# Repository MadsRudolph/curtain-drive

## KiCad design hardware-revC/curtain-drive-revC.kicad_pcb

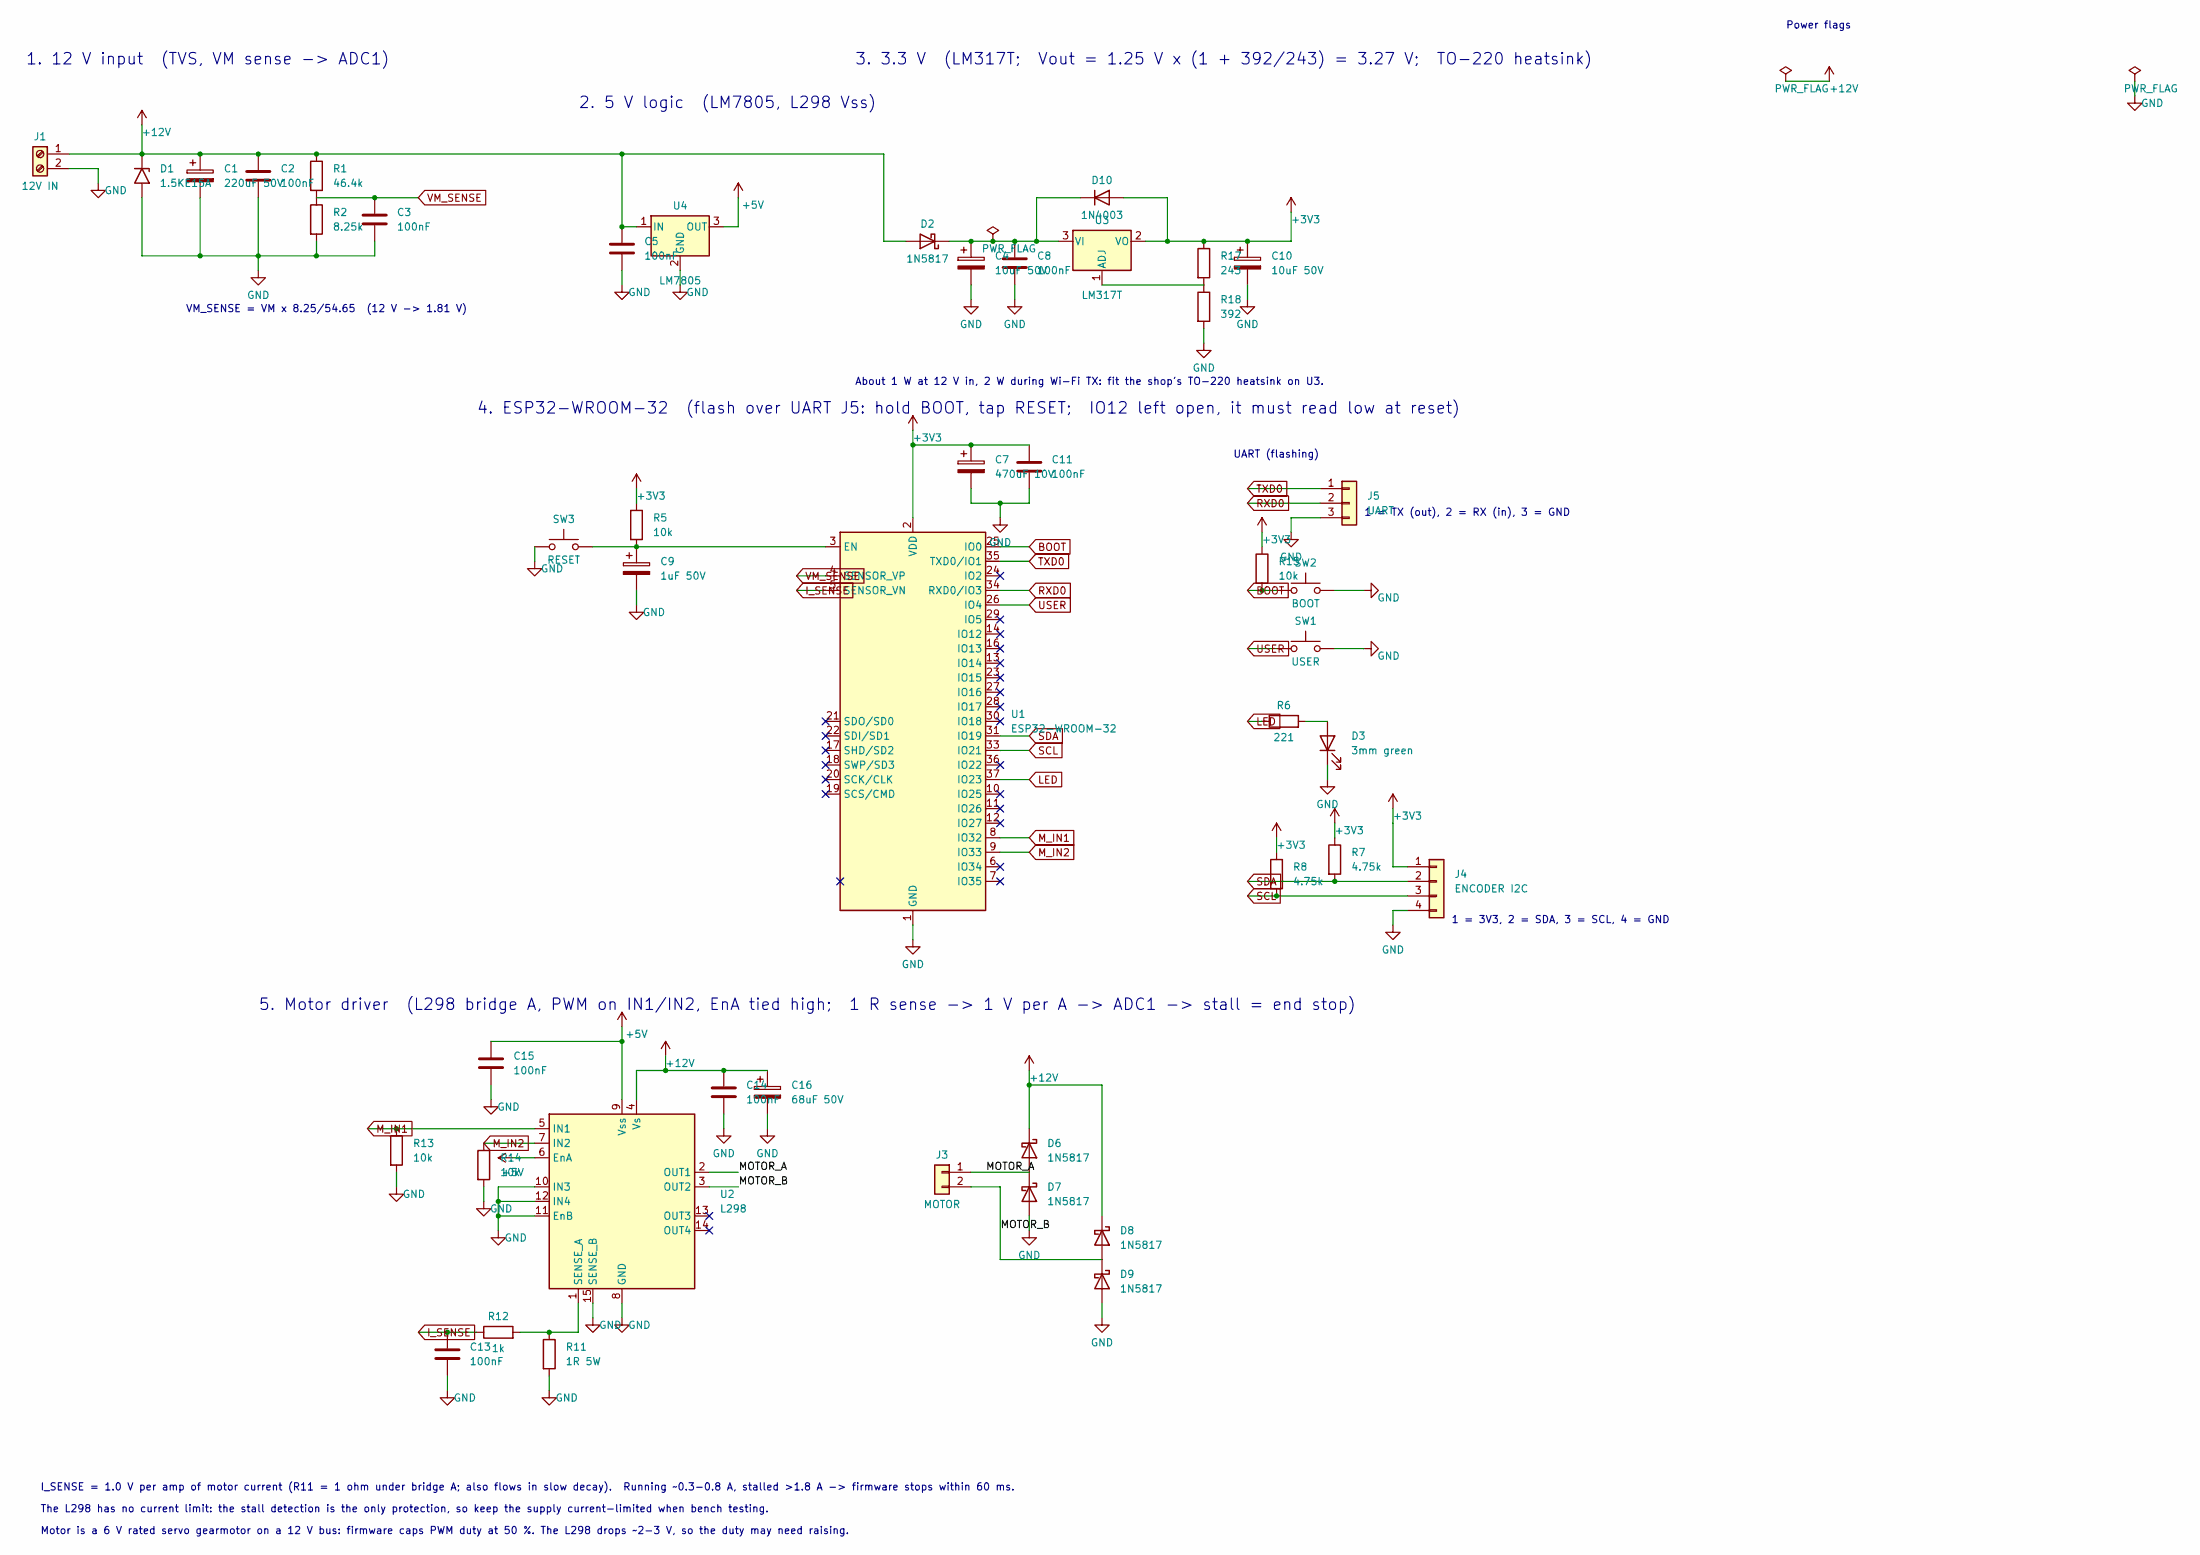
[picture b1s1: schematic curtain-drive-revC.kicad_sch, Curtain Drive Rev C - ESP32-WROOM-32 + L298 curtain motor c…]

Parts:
C1: 220uF 50V; CP_Radial_D10.0mm_P5.00mm
C2, C3, C5, C8, C11, C13, C15: 100nF; C_Disc_D5.0mm_W2.5mm_P5.00mm
C4, C10: 10uF 50V; CP_Radial_D5.0mm_P2.00mm
C7: 470uF 10V; CP_Radial_D8.0mm_P3.50mm
C9: 1uF 50V; CP_Radial_D5.0mm_P2.00mm
C14: 100nF; C_Disc_D5.0mm_W2.5mm_P7.62mm_Bent
C16: 68uF 50V; CP_Radial_D8.0mm_P3.50mm
D1: 1.5KE15A; D_DO-201AE_P15.24mm_Horizontal
D2, D6, D7, D8, D9: 1N5817; D_DO-41_SOD81_P10.16mm_Horizontal
D3: 3mm green; LED_D3.0mm
D10: 1N4003; D_DO-41_SOD81_P10.16mm_Horizontal
J1: 12V IN; TerminalBlock_Phoenix_MKDS-1,5-2-5.08_1x02_P5.08mm_Horizont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
J3: MOTOR; Molex_KK-254_AE-6410-02A_1x02_P2.54mm_Vertical
J4: ENCODER I2C; Molex_KK-254_AE-6410-04A_1x04_P2.54mm_Vertical
J5: UART; PinHeader_1x03_P2.54mm_Vertical
R1: 46.4k; R_Axial_DIN0207_L6.3mm_D2.5mm_P7.62mm_Horizontal
R2: 8.25k; R_Axial_DIN0207_L6.3mm_D2.5mm_P7.62mm_Horizontal
R5, R13, R14, R15: 10k; R_Axial_DIN0207_L6.3mm_D2.5mm_P7.62mm_Horizontal
R6: 221; R_Axial_DIN0207_L6.3mm_D2.5mm_P7.62mm_Horizontal
R7, R8: 4.75k; R_Axial_DIN0207_L6.3mm_D2.5mm_P7.62mm_Horizontal
R11: 1R 5W; R_Axial_Power_L25.0mm_W9.0mm_P27.94mm
R12: 1k; R_Axial_DIN0207_L6.3mm_D2.5mm_P7.62mm_Horizontal
R17: 243; R_Axial_DIN0207_L6.3mm_D2.5mm_P7.62mm_Horizontal
R18: 392; R_Axial_DIN0207_L6.3mm_D2.5mm_P7.62mm_Horizontal
SW1: USER; SW_PUSH_6mm_Jumpers
SW2: BOOT; SW_PUSH_6mm_Jumpers
SW3: RESET; SW_PUSH_6mm_Jumpers
U1: ESP32-WROOM-32; ESP32-WROOM-32_NoVias
U2: L298; TO-220-15_P2.54x5.08mm_StaggerOdd_Lead4.58mm_Vertical
U3: LM317T; TO-220-3_Vertical_Heatsink16x16
U4: LM7805; TO-220-3_Vertical

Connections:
+3V3: C7.1, C10.1, C11.1, D10.2 (A), J4.1, R5.1, R7.1, R8.1, R15.1, R17.1, U1.2 (VDD), U3.2 (VO)
+5V: C15.1, U2.6 (EnA), U2.9 (Vss), U4.3 (OUT)
/MOTOR_A: D6.2 (A), D7.1 (K), J3.1, U2.2 (OUT1)
/MOTOR_B: D8.2 (A), D9.1 (K), J3.2, U2.3 (OUT2)
BOOT: R15.2, SW2.1, U1.25 (IO0)
I_SENSE: C13.1, R12.1, U1.5 (SENSOR_VN)
LED: R6.1, U1.37 (IO23)
M_IN1: R13.1, U1.8 (IO32), U2.5 (IN1)
M_IN2: R14.1, U1.9 (IO33), U2.7 (IN2)
unnamed: D3.2 (A), R6.2
unnamed: C9.1, R5.2, SW3.2, U1.3 (EN)
unnamed: R11.1, R12.2, U2.1 (SENSE_A)
unnamed: R17.2, R18.1, U3.1 (ADJ)
RXD0: J5.2, U1.34 (RXD0/IO3)
SCL: J4.3, R8.2, U1.33 (IO21)
SDA: J4.2, R7.2, U1.31 (IO19)
TXD0: J5.1, U1.35 (TXD0/IO1)
USER: SW1.1, U1.26 (IO4)
VM_SENSE: C3.1, R1.2, R2.1, U1.4 (SENSOR_VP)

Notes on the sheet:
1. 12 V input (TVS, VM sense -> ADC1)
VM_SENSE = VM x 8.25/54.65 (12 V -> 1.81 V)
2. 5 V logic (LM7805, L298 Vss)
3. 3.3 V (LM317T; Vout = 1.25 V x (1 + 392/243) = 3.27 V; TO-220 heatsink)
About 1 W at 12 V in, 2 W during Wi-Fi TX: fit the shop's TO-220 heatsink on U3.
Power flags
4. ESP32-WROOM-32 (flash over UART J5: hold BOOT, tap RESET; IO12 left open, it must read low at reset)
UART (flashing)
1 = TX (out), 2 = RX (in), 3 = GND
1 = 3V3, 2 = SDA, 3 = SCL, 4 = GND
5. Motor driver (L298 bridge A, PWM on IN1/IN2, EnA tied high; 1 R sense -> 1 V per A -> ADC1 -> stall = end stop)
I_SENSE = 1.0 V per amp of motor current (R11 = 1 ohm under bridge A; also flows in slow decay). Running ~0.3-0.8 A, stalled >1.8 A -> firmware stops within 60 ms.
The L298 has no current limit: the stall detection is the only protection, so keep the supply current-limited when bench testing.
Motor is a 6 V rated servo gearmotor on a 12 V bus: firmware caps PWM duty at 50 %. The L298 drops ~2-3 V, so the duty may need raising.

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
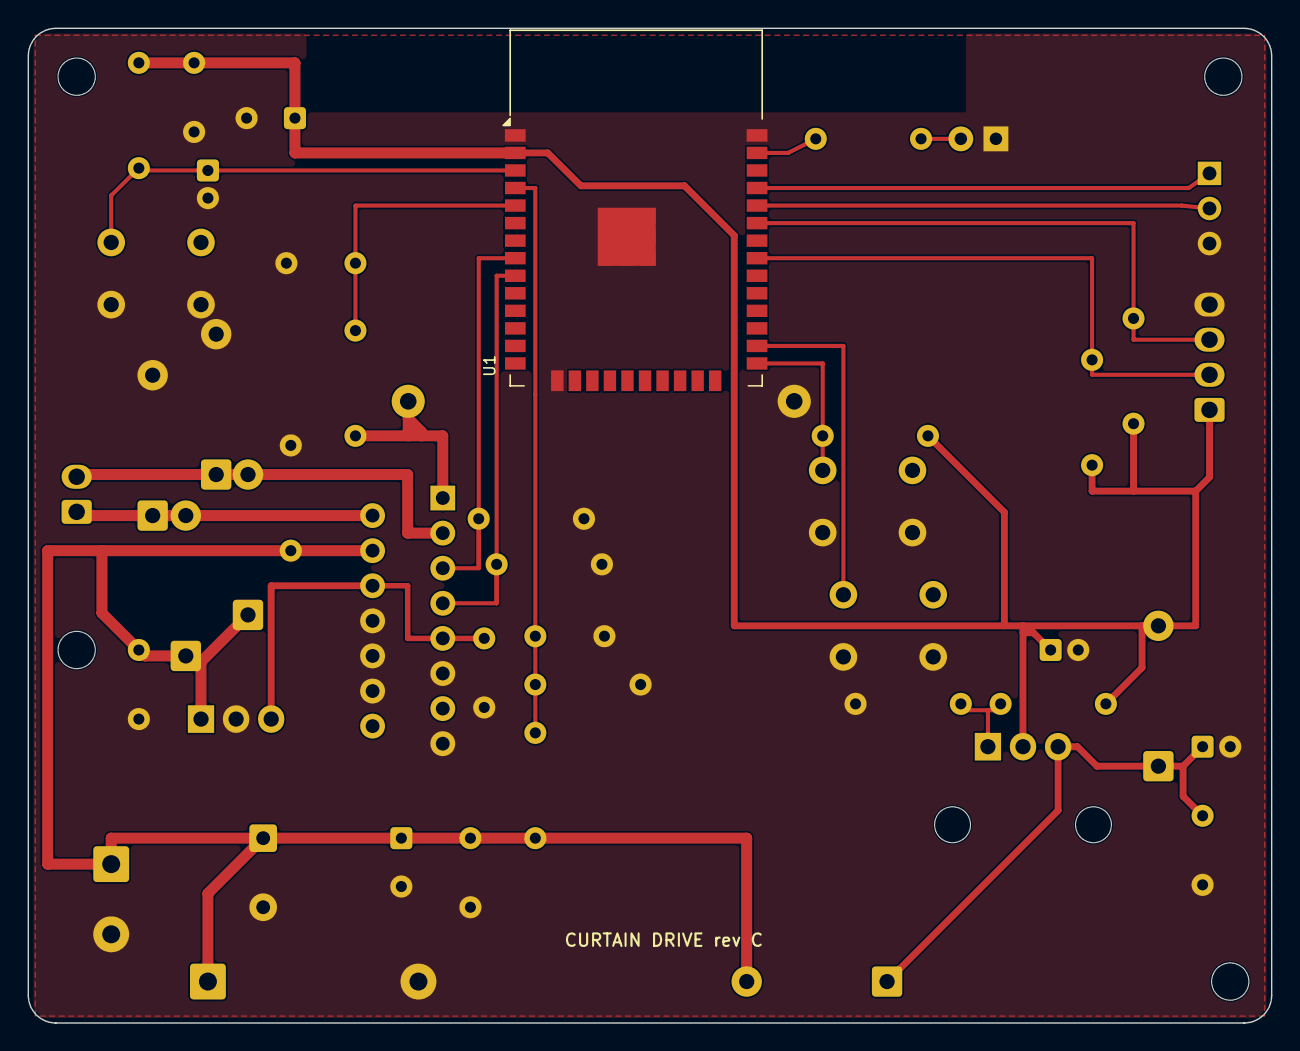
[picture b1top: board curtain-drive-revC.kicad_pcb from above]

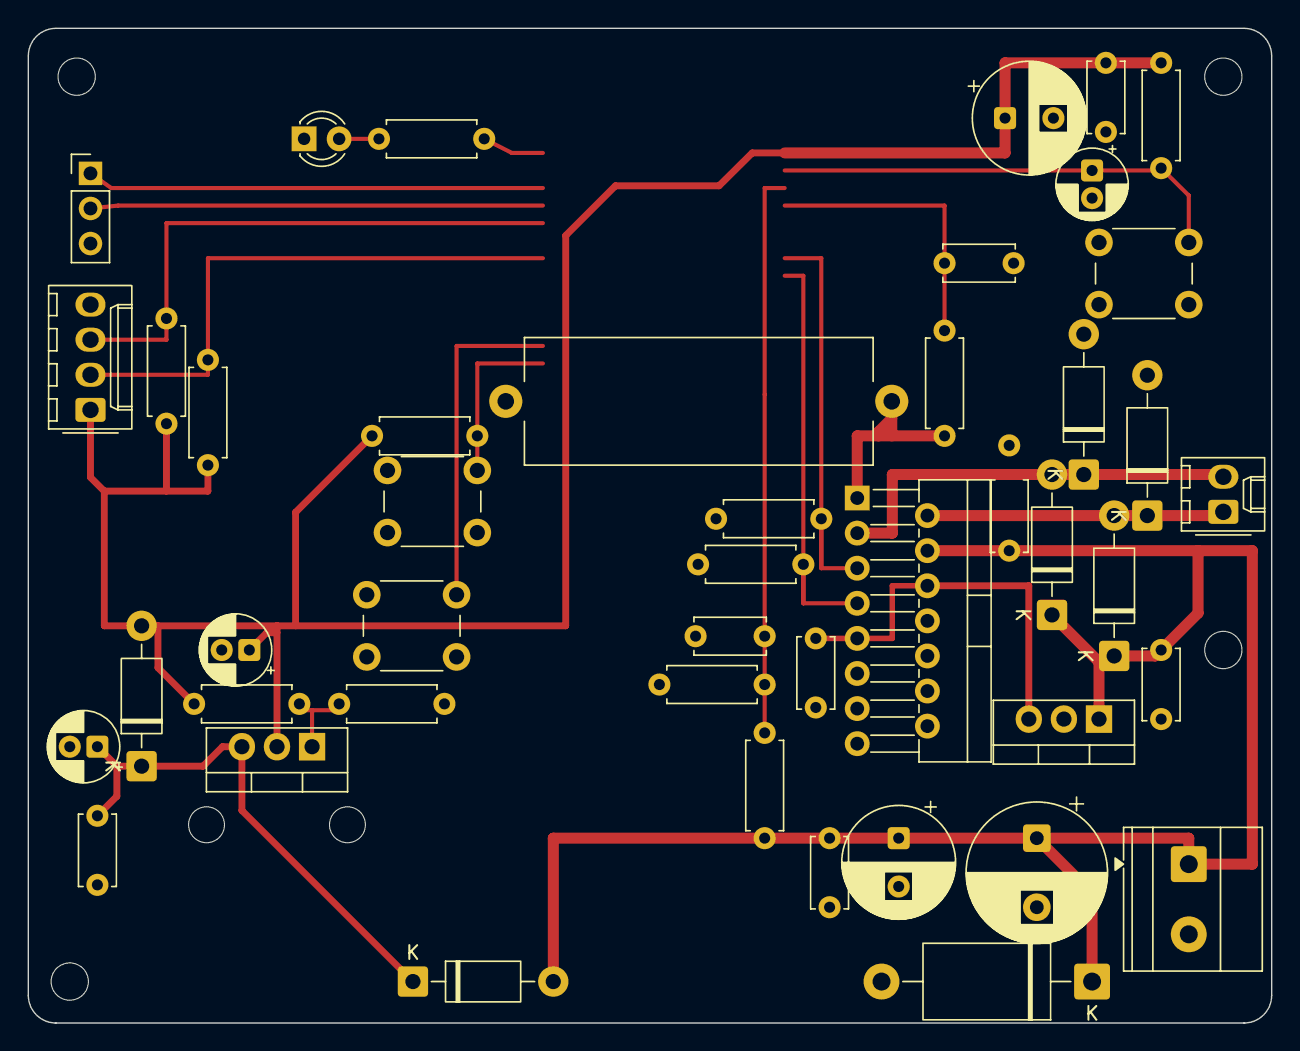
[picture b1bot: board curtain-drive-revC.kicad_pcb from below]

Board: 2 copper layers, 90.0 x 72.0 mm, 50 parts (45 on the bottom side), 22 nets.

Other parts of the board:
H1, H2, H3, H4: MountingHole_2.7mm_M2.5

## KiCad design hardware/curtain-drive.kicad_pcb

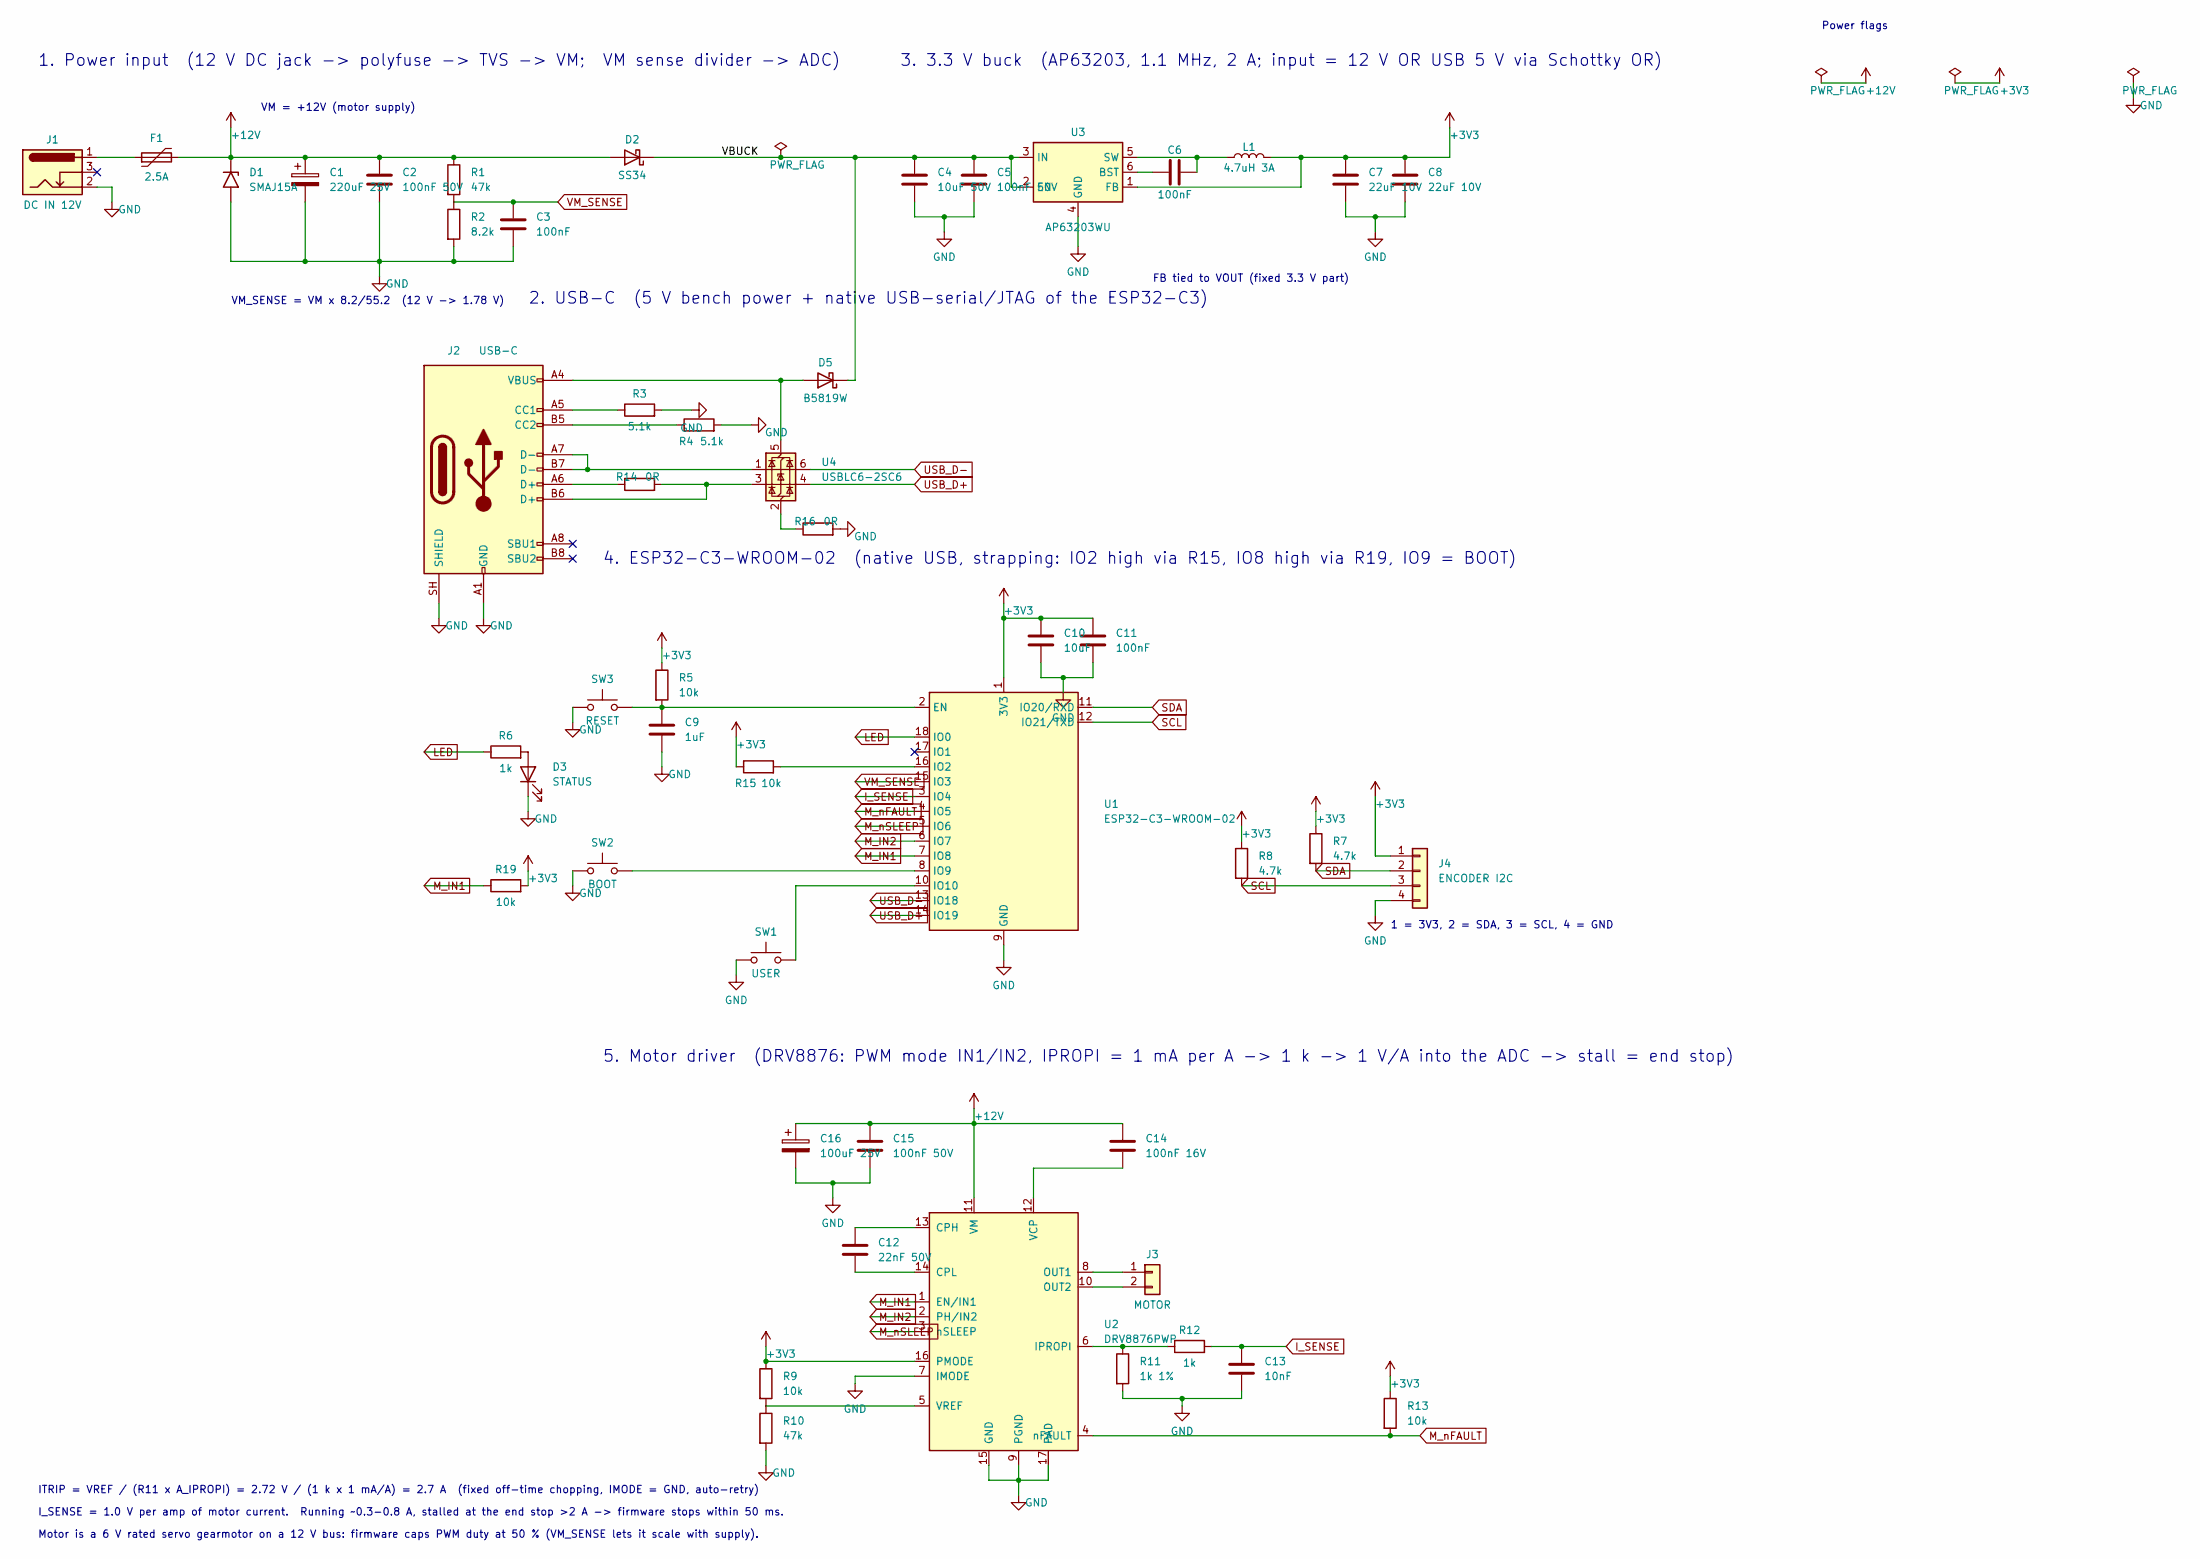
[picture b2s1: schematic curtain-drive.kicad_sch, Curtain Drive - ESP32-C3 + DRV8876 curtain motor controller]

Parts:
C1: 220uF 25V; CP_Elec_8x10
C2, C5, C15: 100nF 50V; C_0603_1608Metric
C3, C6, C11: 100nF; C_0603_1608Metric
C4: 10uF 50V; C_1206_3216Metric
C7, C8: 22uF 10V; C_0805_2012Metric
C9: 1uF; C_0603_1608Metric
C10: 10uF; C_0805_2012Metric
C12: 22nF 50V; C_0603_1608Metric
C13: 10nF; C_0603_1608Metric
C14: 100nF 16V; C_0603_1608Metric
C16: 100uF 25V; CP_Elec_6.3x7.7
D1: SMAJ15A; D_SMA
D2: SS34; D_SMA
D3: STATUS; LED_0603_1608Metric
D5: B5819W; D_SOD-123
F1: 2.5A; Fuse_1812_4532Metric
J1: DC IN 12V; BarrelJack_CUI_PJ-036AH-SMT_Horizontal
J2: USB-C; USB_C_Receptacle_HRO_TYPE-C-31-M-12_1L
J3: MOTOR; JST_PH_B2B-PH-SM4-TB_1x02-1MP_P2.00mm_Vertical
J4: ENCODER I2C; JST_PH_B4B-PH-SM4-TB_1x04-1MP_P2.00mm_Vertical
L1: 4.7uH 3A; L_Sunlord_MWSA0503S
R1: 47k; R_1206_3216Metric
R2: 8.2k; R_0603_1608Metric
R3: 5.1k; R_0805_2012Metric
R4: 5.1k; R_0603_1608Metric
R5, R15, R19: 10k; R_0603_1608Metric
R6, R12: 1k; R_0603_1608Metric
R7, R8: 4.7k; R_0603_1608Metric
R9, R13: 10k; R_0805_2012Metric
R10: 47k; R_0805_2012Metric
R11: 1k 1%; R_0603_1608Metric
R14: 0R; R_0603_1608Metric
R16: 0R; R_0805_2012Metric
SW1: USER; SW_SPST_PTS645Sx43SMTR92_Jumpers
SW2: BOOT; SW_SPST_PTS645Sx43SMTR92_Jumpers
SW3: RESET; SW_SPST_PTS645Sx43SMTR92_Jumpers
U1: ESP32-C3-WROOM-02; ESP32-C3-WROOM-02_NoVias
U2: DRV8876PWP; HTSSOP-16-1EP_4.4x5mm_P0.65mm_EP3.4x5mm_Mask2.46x2.31mm
U3: AP63203WU; TSOT-23-6
U4: USBLC6-2SC6; SOT-23-6

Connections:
I_SENSE: C13.1, R12.2, U1.3 (IO4)
LED: R6.1, U1.18 (IO0)
M_IN1: R19.1, U1.7 (IO8), U2.1 (EN/IN1)
M_IN2: U1.6 (IO7), U2.2 (PH/IN2)
M_nFAULT: R13.2, U1.4 (IO5), U2.4 (nFAULT)
M_nSLEEP: U1.5 (IO6), U2.3 (nSLEEP)
unnamed: D3.2 (A), R6.2
unnamed: D5.2 (A), J2.A4 (VBUS), J2.A9 (VBUS), J2.B4 (VBUS), J2.B9 (VBUS), U4.5 (VBUS)
unnamed: F1.1, J1.1
unnamed: J2.A5 (CC1), R3.1
unnamed: J2.B5 (CC2), R4.1
unnamed: J2.A6 (D+), R14.1
unnamed: J2.B6 (D+), R14.2, U4.3 (I/O2)
unnamed: J2.A7 (D-), J2.B7 (D-), U4.1 (I/O1)
unnamed: J3.1, U2.8 (OUT1)
unnamed: J3.2, U2.10 (OUT2)
unnamed: C9.1, R5.2, SW3.2, U1.2 (EN)
unnamed: R15.2, U1.16 (IO2)
unnamed: SW2.2, U1.8 (IO9)
unnamed: SW1.2, U1.10 (IO10)
unnamed: C12.1, U2.13 (CPH)
unnamed: C12.2, U2.14 (CPL)
unnamed: R11.1, R12.1, U2.6 (IPROPI)
unnamed: C14.2, U2.12 (VCP)
unnamed: R9.2, R10.1, U2.5 (VREF)
unnamed: C6.1, U3.6 (BST)
unnamed: C6.2, L1.1, U3.5 (SW)
unnamed: R16.1, U4.2 (GND)
SCL: J4.3, R8.2, U1.12 (IO21/TXD)
SDA: J4.2, R7.2, U1.11 (IO20/RXD)
USB_D+: U1.14 (IO19), U4.4 (I/O2)
USB_D-: U1.13 (IO18), U4.6 (I/O1)
VM_SENSE: C3.1, R1.2, R2.1, U1.15 (IO3)

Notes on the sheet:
1. Power input (12 V DC jack -> polyfuse -> TVS -> VM; VM sense divider -> ADC)
VM = +12V (motor supply)
VM_SENSE = VM x 8.2/55.2 (12 V -> 1.78 V)
2. USB-C (5 V bench power + native USB-serial/JTAG of the ESP32-C3)
3. 3.3 V buck (AP63203, 1.1 MHz, 2 A; input = 12 V OR USB 5 V via Schottky OR)
FB tied to VOUT (fixed 3.3 V part)
Power flags
4. ESP32-C3-WROOM-02 (native USB, strapping: IO2 high via R15, IO8 high via R19, IO9 = BOOT)
1 = 3V3, 2 = SDA, 3 = SCL, 4 = GND
5. Motor driver (DRV8876: PWM mode IN1/IN2, IPROPI = 1 mA per A -> 1 k -> 1 V/A into the ADC -> stall = end stop)
ITRIP = VREF / (R11 x A_IPROPI) = 2.72 V / (1 k x 1 mA/A) = 2.7 A (fixed off-time chopping, IMODE = GND, auto-retry)
I_SENSE = 1.0 V per amp of motor current. Running ~0.3-0.8 A, stalled at the end stop >2 A -> firmware stops within 50 ms.
Motor is a 6 V rated servo gearmotor on a 12 V bus: firmware caps PWM duty at 50 % (VM_SENSE lets it scale with supply).

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
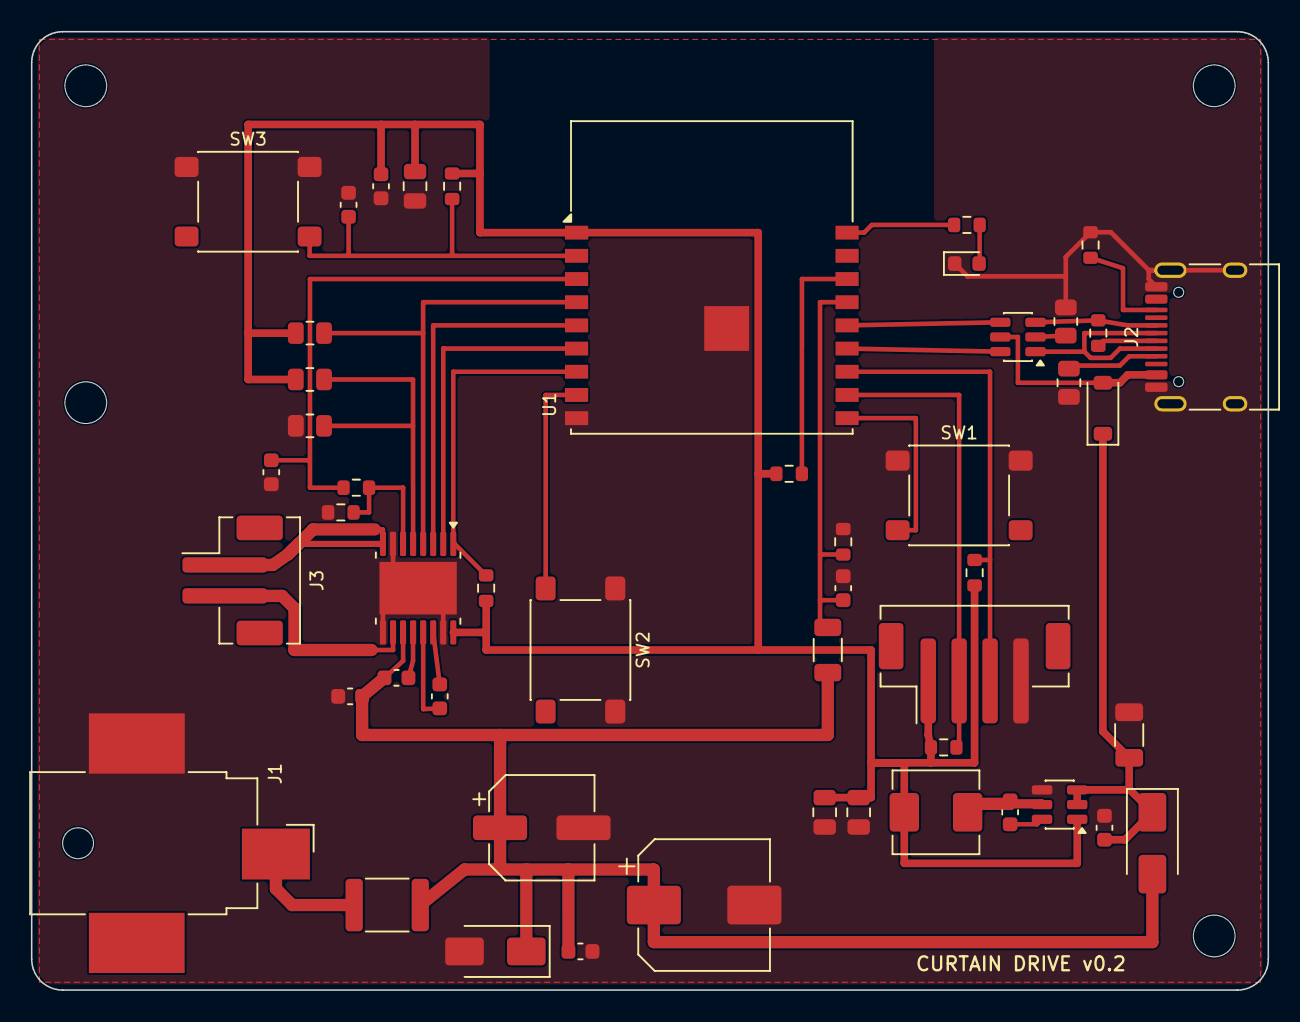
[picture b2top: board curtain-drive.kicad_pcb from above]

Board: 2 copper layers, 80.0 x 62.0 mm, 54 parts (0 on the bottom side), 37 nets.

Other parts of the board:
H1, H2, H3, H4: MountingHole_2.7mm_M2.5

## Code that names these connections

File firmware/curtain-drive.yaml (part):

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#
# Pin map (see hardware/curtain-drive.kicad_sch; chosen so the single-sided board
# routes without crossings):
#   GPIO8  M_IN1     DRV8876 IN1 (PWM), R19 pull-up keeps the strap high at boot
#   GPIO7  M_IN2     DRV8876 IN2 (PWM)
#   GPIO6  M_nSLEEP  driver enable (high = on)  GPIO5  M_nFAULT driver fault, open drain, active low
#   GPIO4  I_SENSE   IPROPI x 1 k -> 1.0 V per A of motor current
#   GPIO3  VM_SENSE  12 V rail / vm_divider (Rev B 46.4k : 8.25k; Rev A 47k : 8.2k)
#   GPIO0  status LED (active high)             GPIO9  BOOT button
#   GPIO10 USER button (active low)             GPIO20 SDA, GPIO21 SCL (optional AS5600 encoder)
#   GPIO2  strapping pin, held high by R15, unused
#
# End stop principle: the DRV8876 mirrors the motor current onto IPROPI. Along the
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
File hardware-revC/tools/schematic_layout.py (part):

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sh.gnd((c2.x, RAIL_A))
sh.seg((r1.x, YP + 7.62), (c3.x, YP + 7.62))
sh.seg((c3.x, YP + 7.62), (G(62), YP + 7.62))
sh.label((G(62), YP + 7.62), "VM_SENSE", kind="global")
sh.seg(j1.pin(1), (G(126), YP))                      # the +12 V bus, across the band
sh.rail((X_TVS, YP), net="+12V", rise=5.08)
sh.note((G(30), RAIL_A + G(8)), "VM_SENSE = VM x 8.25/54.65  (12 V -> 1.81 V)")
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sh.seg(sw3.pin(2), (XEN, pen.y))
sh.gnd(sw3.pin(1))
# ADC1 inputs (the only ADC usable with Wi-Fi on) on the sensor pins
for pin, name in (("SENSOR_VP", "VM_SENSE"), ("SENSOR_VN", "I_SENSE")):
    p = u1.pin(pin)
    sh.seg(p, (p.x - G(4), p.y))
    sh.label((p.x - G(4), p.y), name, kind="global")
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    sh.nc(u1.pin(pin))
# right-hand pins leave as global labels
XR = XU + G(16)
for pin, name in (("IO0", "BOOT"), ("TXD0/IO1", "TXD0"), ("RXD0/IO3", "RXD0"), ("IO4", "USER"),
                  ("IO19", "SDA"), ("IO21", "SCL"), ("IO23", "LED"),
                  ("IO32", "M_IN1"), ("IO33", "M_IN2")):
    p = u1.pin(pin)
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p1, p2 = u2.pin("IN1"), u2.pin("IN2")
XA13, XB14 = XL - G(31), XL - G(19)          # IN2 stops short so R13 can hang from IN1
sh.seg(p1, (XL - G(35), p1.y))
sh.label((XL - G(35), p1.y), "M_IN1", kind="global")
sh.seg(p2, (XB14, p2.y))
sh.label((XB14, p2.y), "M_IN2", kind="global")
r13 = hang("Device:R", "R13", XA13, p1.y, "10k", RAX)
r14 = hang("Device:R", "R14", XB14, p2.y, "10k", RAX)
sh.gnd(r13.pin(2))
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sh.seg(r12.pin(1), (XIS - G(4), YS))
c13 = hang("Device:C", "C13", XIS, YS, "100nF", CDISC)
sh.gnd(c13.pin(2))
sh.label((XIS - G(4), YS), "I_SENSE", kind="global")
# outputs -> motor block
for pin, name in (("OUT1", "MOTOR_A"), ("OUT2", "MOTOR_B")):
    p = u2.pin(pin)
    sh.seg(p, (p.x + G(4), p.y))
    sh.label((p.x + G(4), p.y), name)
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YBn = j3.pin(2).y + G(10)
Y12 = YA - G(12)
sh.seg(j3.pin(1), (XA, YA))
sh.label((XJ + G(6), YA), "MOTOR_A")
sh.seg(j3.pin(2), (XJ + G(8), j3.pin(2).y))
sh.seg((XJ + G(8), j3.pin(2).y), (XJ + G(8), YBn))
sh.seg((XJ + G(8), YBn), (XBB, YBn))
sh.label((XJ + G(8), YBn - G(4)), "MOTOR_B")
d6 = diode_up("D6", XA, YA, "1N5817", DO41)             # MOTOR_A -> +12V
d7 = diode_up("D7", XA, YA + 7.62, "1N5817", DO41)      # GND -> MOTOR_A
d8 = diode_up("D8", XBB, YBn, "1N5817", DO41)           # MOTOR_B -> +12V
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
